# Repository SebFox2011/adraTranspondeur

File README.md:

# adraTranspondeur

  Project for sending morse message with a variable delay.
  Pin 13 : Output: morse message
  Pin 12 : Output: PTT activation
  Pin 11 : Input: 0 220V mode, +5V: Battery mode 

  By Sébastien PHILIPPE - F4JRN

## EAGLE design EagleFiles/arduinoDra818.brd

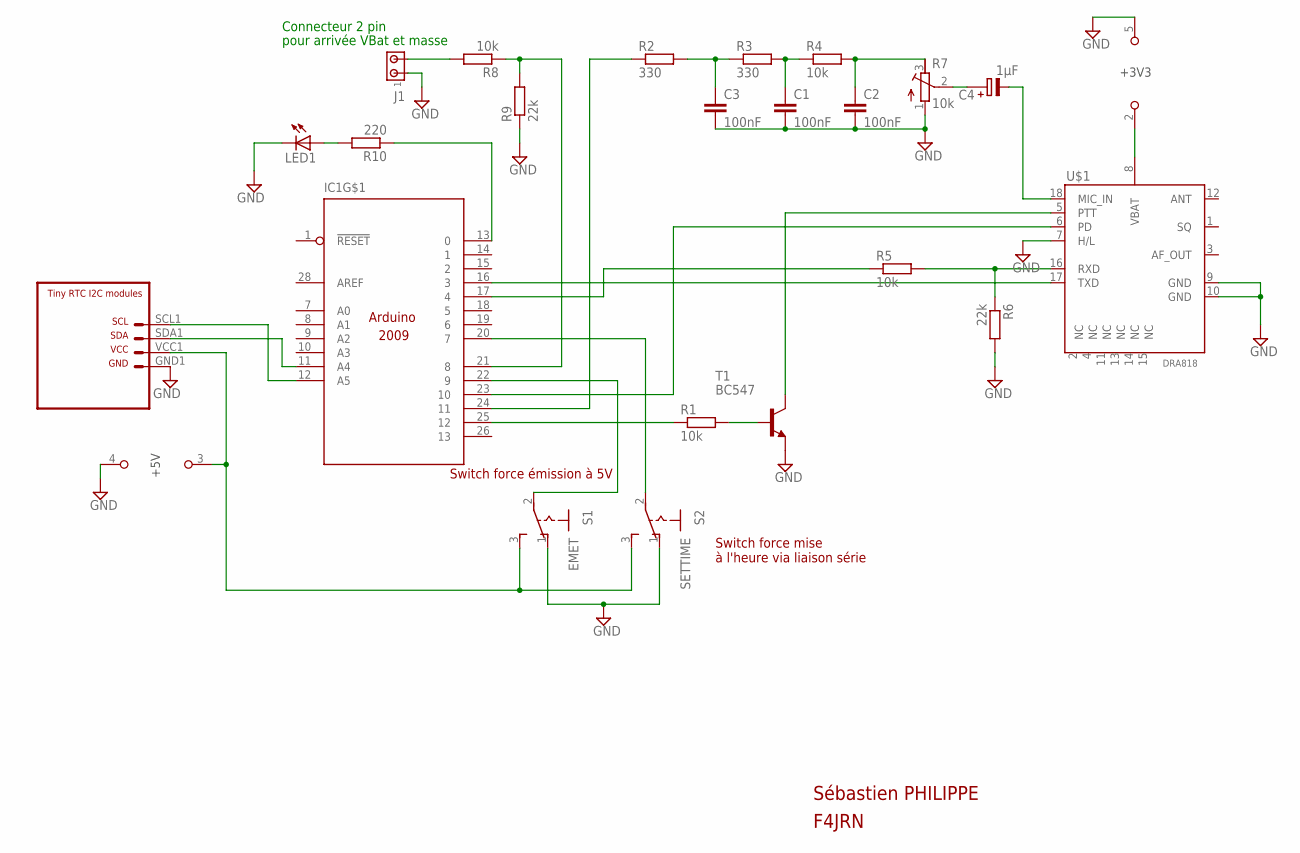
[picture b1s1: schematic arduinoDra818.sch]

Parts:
C1, C2, C3: 100nF; C050-025X075
C4: 1µF; E2,0-5
IC1: Arduino; ARDUINO2009_1
J1: MTA02-100; 10X02MTA
LED1: LED3MM
R1, R4, R5, R8: 10k; 0411/15
R2, R3: 330; 0411/15
R6, R9: 22k; 0411/15
R7: 10k; RTRIM3339P
R10: 220; 0411/15
S1: EMET; 255SB
S2: SETTIME; 255SB
T1: BC547; TO92
U$1: DRA818; DRA818A
U$2: RTC

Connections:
+5V: IC1.3 (+5V), S1.3 (S), S2.3 (S), U$2.VCC1
+VIN: IC1.6 (+VIN)
GND: C1.2, C2.2, C3.2, IC1.4 (GND), IC1.5 (GND), IC1.27 (GND), J1.1, LED1.K (C), R6.2, R7.1 (E), R9.1, S1.1 (O), S2.1 (O), T1.1 (E), U$1.7 (H/L), U$1.9 (GND), U$1.10 (GND), U$2.GND1
unnamed: IC1.25 (12), R1.1
unnamed: R1.2, T1.2 (B)
unnamed: IC1.24 (11), R2.1
unnamed: IC1.17 (4), R5.1
unnamed: IC1.12 (A5), U$2.SCL1
unnamed: IC1.11 (A4), U$2.SDA1
unnamed: IC1.2 (+3V3), U$1.8 (VBAT)
unnamed: C4.-, U$1.18 (MIC_IN)
unnamed: T1.3 (C), U$1.5 (PTT)
unnamed: IC1.16 (3), U$1.17 (TXD)
unnamed: C3.1, R2.2, R3.1
unnamed: R5.2, R6.1, U$1.16 (RXD)
unnamed: J1.2, R8.2
unnamed: C1.1, R3.2, R4.1
unnamed: C2.1, R4.2, R7.3 (A)
unnamed: C4.+, R7.2 (S)
unnamed: IC1.23 (10), U$1.6 (PD)
unnamed: IC1.21 (8), R8.1, R9.2
unnamed: IC1.22 (9), S1.2
unnamed: IC1.20 (7), S2.2
unnamed: IC1.13 (0), R10.1
unnamed: LED1.A, R10.2

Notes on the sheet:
Sébastien PHILIPPE
F4JRN
Switch force mise à l'heure via liaison série
Switch force émission à 5V
Connecteur 2 pin
pour arrivée VBat et masse

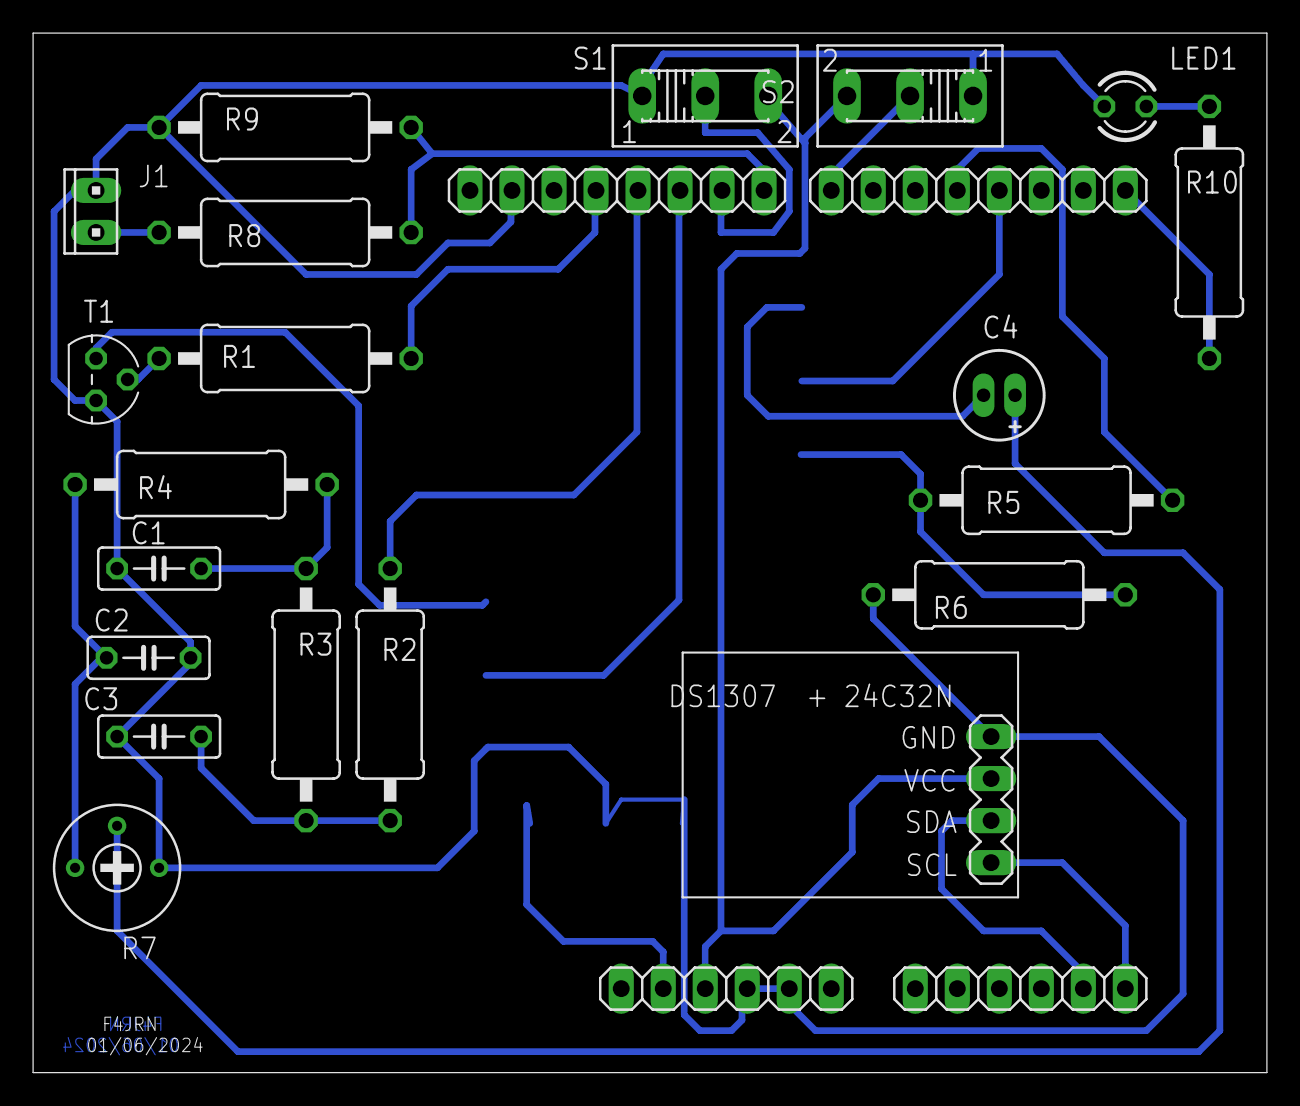
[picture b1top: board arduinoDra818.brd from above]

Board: 2 copper layers, 74.6 x 62.9 mm, 22 parts (1 on the bottom side), 24 nets.

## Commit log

2023-01-22 Change variable type for optimisation
2023-02-28 Ajout de la gestion du DRA818
2023-02-28 Correction dra818.c
2023-03-02 Mise au point pour l'émission
2023-03-02 Programme envoi d'un message morse sur le dra818
2023-03-10 Add files via upload
    Ajout de la fonction tone, et envoi du signal morse sur une pin PWM
2023-03-10 Passage à la librairie cww_MorseTx pour simplifier le code
2023-03-10 Gestion du rtc et envoie du signal morse à des heures précises.
2023-03-12 Correction config DRA818 & SETTIME
2023-03-18 Ajout du schéma électrique du montage
2023-03-22 Correction de la broche rx du dra vers arduino
2024-05-12 update arduinoDra818 filter bf
2024-06-01 Add eagle files - schema board and gerber files

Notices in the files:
parts and their libraries:
cap-pan40: Copyright (C) 2004, Bob Starr
